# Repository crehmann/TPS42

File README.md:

# TPS42

TPS42 is a 42/36 keys ergonomic split keyboard. The outer pinky columns can be broken off. The main goal for desing it was to have a low profile split keyboard with an integrated TrackPoint module

## Features
- Integrated TrackPoint reset circuit and the option to mount a TrackPoint to the bottom of the PCB (between the two inner columns)
- I2C interface for an OLED display
- Wireless Ready (however, without TrackPoint support):
  - Battery switch / connector
  - Option to use a battery friendly Sharp memory display instead of an OLED display
- Choc-spaced
- Partially hot swap sockets supported (except for two switches around the TrackPoint module)

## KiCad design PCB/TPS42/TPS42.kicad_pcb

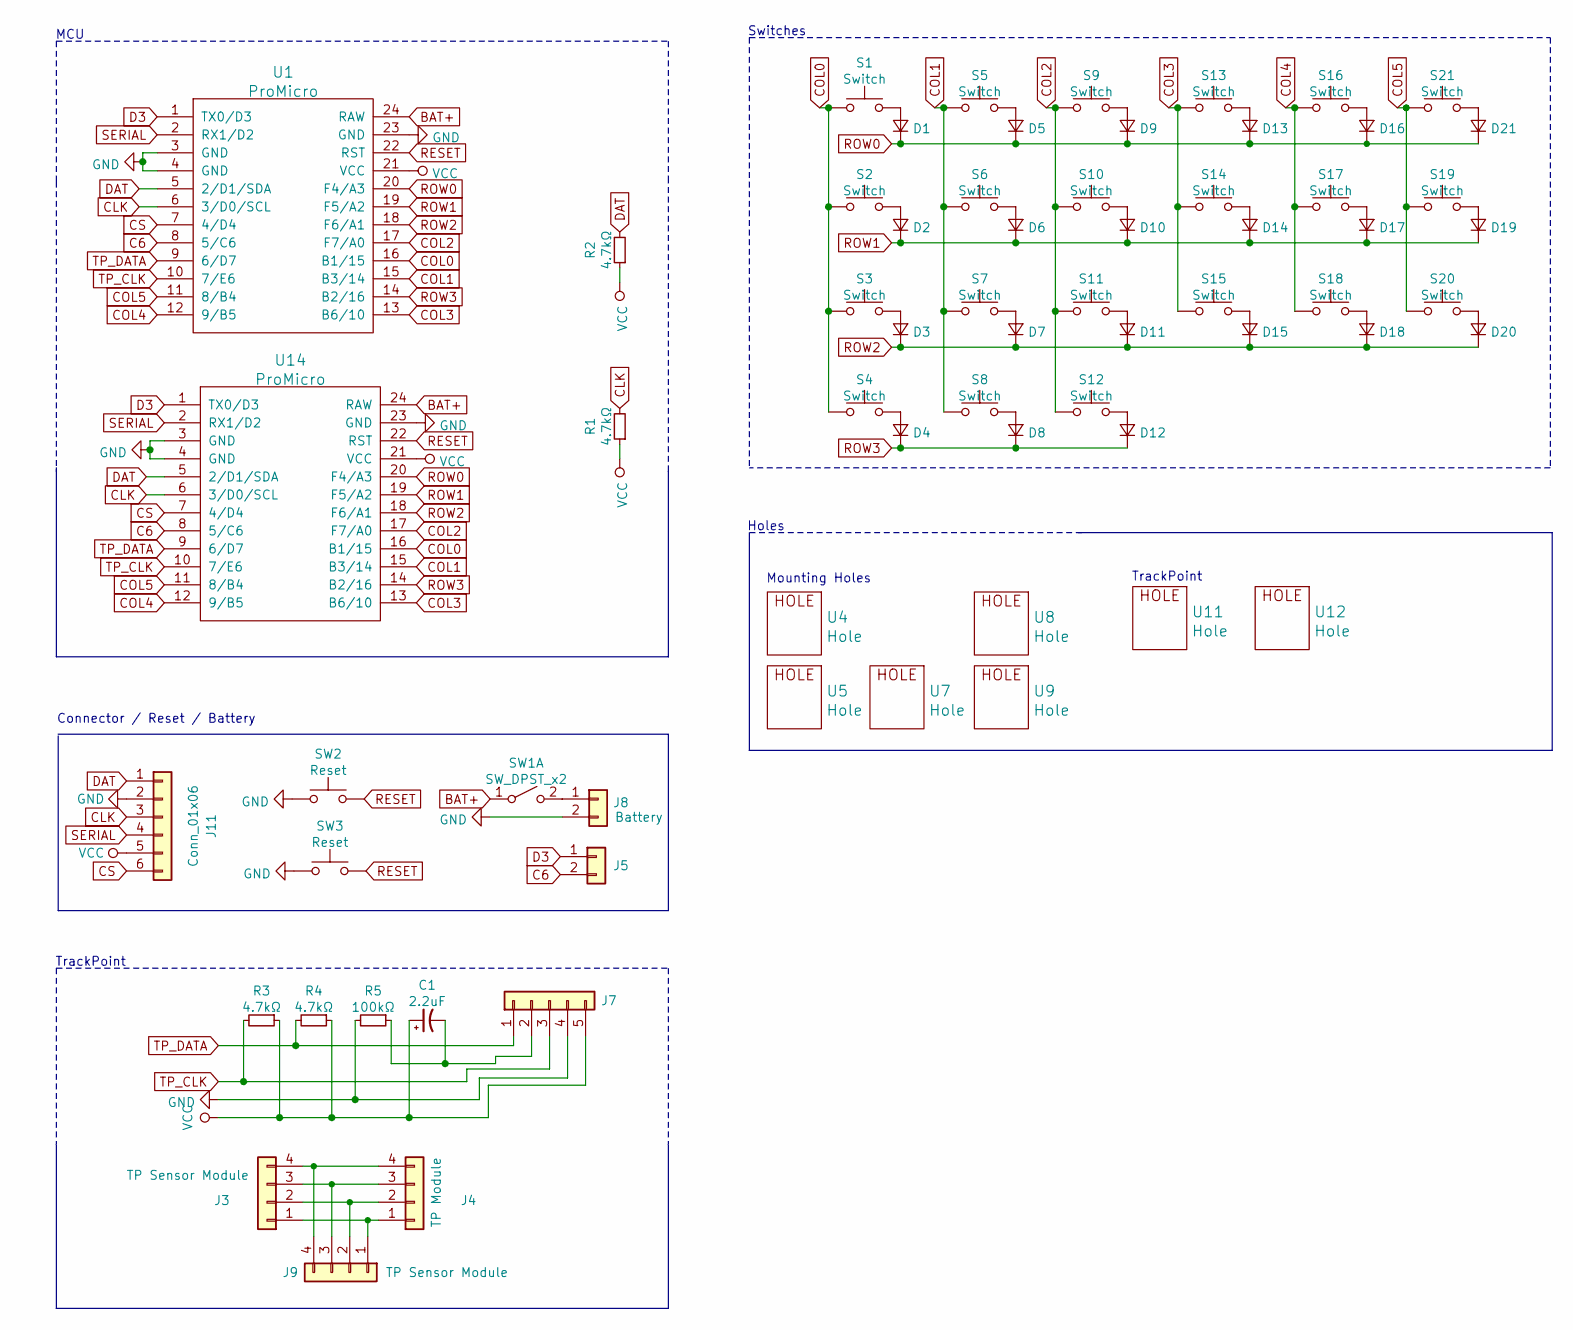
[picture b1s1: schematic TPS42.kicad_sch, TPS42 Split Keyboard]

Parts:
C1: 2.2uF; C_0603_1608Metric_Pad1.08x0.95mm_HandSolder_Reversable
D1, D2, D3, D4, D5, D6, D7, D8, D9, D10, D11, D12, D13, D14, D15, D16, D17, D18, D19, D20, D21: D_Small; D_SOD-323_HandSoldering_Reversable
J3, J9: TP Sensor Module; TPSensorModule_Connector
J4: TP Module; TPSensorModule_Connector
J5: Conn_01x02; PinHeader_1x02_P2.54mm_Vertical
J7: TrackPoint; TPModule
J8: Battery; PinHeader_1x02_P2.54mm_Vertical
J11: Conn_01x06; PinHeader_2x03_P2.54mm_Vertical
R1, R2, R3, R4: 4.7kΩ; R_0603_1608Metric_Pad0.98x0.95mm_HandSolder_Reversable
R5: 100kΩ; R_0603_1608Metric_Pad0.98x0.95mm_HandSolder_Reversable
S1, S6: Switch; SW_PG1350_reversible
S2, S3, S5, S7, S8, S9, S10, S11, S12, S13, S14, S15, S16, S17, S18, S19, S20, S21: Switch; Kailh_socket_PG1350_optional_reversible.kicad_mod
S4: Switch; Kailh_socket_PG1350_125_optional_reversible.kicad_mod
SW1: SW_DPST_x2; SW-TH_3P-L9.1-W3.5-P2.50-S3.20-A3
SW2, SW3: Reset; SMD-SW-4_5.1x5.1x2.5
U1: ProMicro; ProMicro_Flipped_v2_A
U4, U5, U7, U8, U9, U12: Hole; HOLE_M2_TH
U11: Hole; TPSensorModule
U14: ProMicro; ProMicro_Flipped_v2_B

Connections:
BAT+: SW1.1 (A), U1.24 (RAW), U14.24 (RAW)
C6: J5.2, U1.8 (5/C6), U14.8 (5/C6)
CLK: J11.3, R1.2, U1.6 (3/D0/SCL), U14.6 (3/D0/SCL)
COL0: S1.1, S2.1, S3.1, S4.1, U1.16 (B1/15), U14.16 (B1/15)
COL1: S5.1, S6.1, S7.1, S8.1, U1.15 (B3/14), U14.15 (B3/14)
COL2: S9.1, S10.1, S11.1, S12.1, U1.17 (F7/A0), U14.17 (F7/A0)
COL3: S13.1, S14.1, S15.1, U1.13 (B6/10), U14.13 (B6/10)
COL4: S16.1, S17.1, S18.1, U1.12 (9/B5), U14.12 (9/B5)
COL5: S19.1, S20.1, S21.1, U1.11 (8/B4), U14.11 (8/B4)
CS: J11.6, U1.7 (4/D4), U14.7 (4/D4)
D3: J5.1, U1.1 (TX0/D3), U14.1 (TX0/D3)
DAT: J11.1, R2.2, U1.5 (2/D1/SDA), U14.5 (2/D1/SDA)
GND: J7.4, J8.2, J11.2, R5.2, SW2.1, SW3.1, U1.3 (GND), U1.4 (GND), U1.23 (GND), U14.3 (GND), U14.4 (GND), U14.23 (GND)
unnamed: C1.2, J7.2, R5.1
unnamed: D1.2 (A), S1.2
unnamed: D2.2 (A), S2.2
unnamed: D3.2 (A), S3.2
unnamed: D4.2 (A), S4.2
unnamed: D5.2 (A), S5.2
unnamed: D6.2 (A), S6.2
unnamed: D7.2 (A), S7.2
unnamed: D8.2 (A), S8.2
unnamed: D9.2 (A), S9.2
unnamed: D10.2 (A), S10.2
unnamed: D11.2 (A), S11.2
unnamed: D12.2 (A), S12.2
unnamed: D13.2 (A), S13.2
unnamed: D14.2 (A), S14.2
unnamed: D15.2 (A), S15.2
unnamed: D16.2 (A), S16.2
unnamed: D17.2 (A), S17.2
unnamed: D18.2 (A), S18.2
unnamed: D19.2 (A), S19.2
unnamed: D20.2 (A), S20.2
unnamed: D21.2 (A), S21.2
unnamed: J3.1, J4.1, J9.1
unnamed: J3.2, J4.2, J9.2
unnamed: J3.3, J4.3, J9.3
unnamed: J3.4, J4.4, J9.4
unnamed: J8.1, SW1.2 (B)
RESET: SW2.2, SW3.2, U1.22 (RST), U14.22 (RST)
ROW0: D1.1 (K), D5.1 (K), D9.1 (K), D13.1 (K), D16.1 (K), D21.1 (K), U1.20 (F4/A3), U14.20 (F4/A3)
ROW1: D2.1 (K), D6.1 (K), D10.1 (K), D14.1 (K), D17.1 (K), D19.1 (K), U1.19 (F5/A2), U14.19 (F5/A2)
ROW2: D3.1 (K), D7.1 (K), D11.1 (K), D15.1 (K), D18.1 (K), D20.1 (K), U1.18 (F6/A1), U14.18 (F6/A1)
ROW3: D4.1 (K), D8.1 (K), D12.1 (K), U1.14 (B2/16), U14.14 (B2/16)
SERIAL: J11.4, U1.2 (RX1/D2), U14.2 (RX1/D2)
TP_CLK: J7.3, R3.2, U1.10 (7/E6), U14.10 (7/E6)
TP_DATA: J7.1, R4.2, U1.9 (6/D7), U14.9 (6/D7)
VCC: C1.1, J7.5, J11.5, R1.1, R2.1, R3.1, R4.1, U1.21 (VCC), U14.21 (VCC)

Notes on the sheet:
Holes
TrackPoint
Connector / Reset / Battery
Mounting Holes
Switches
MCU

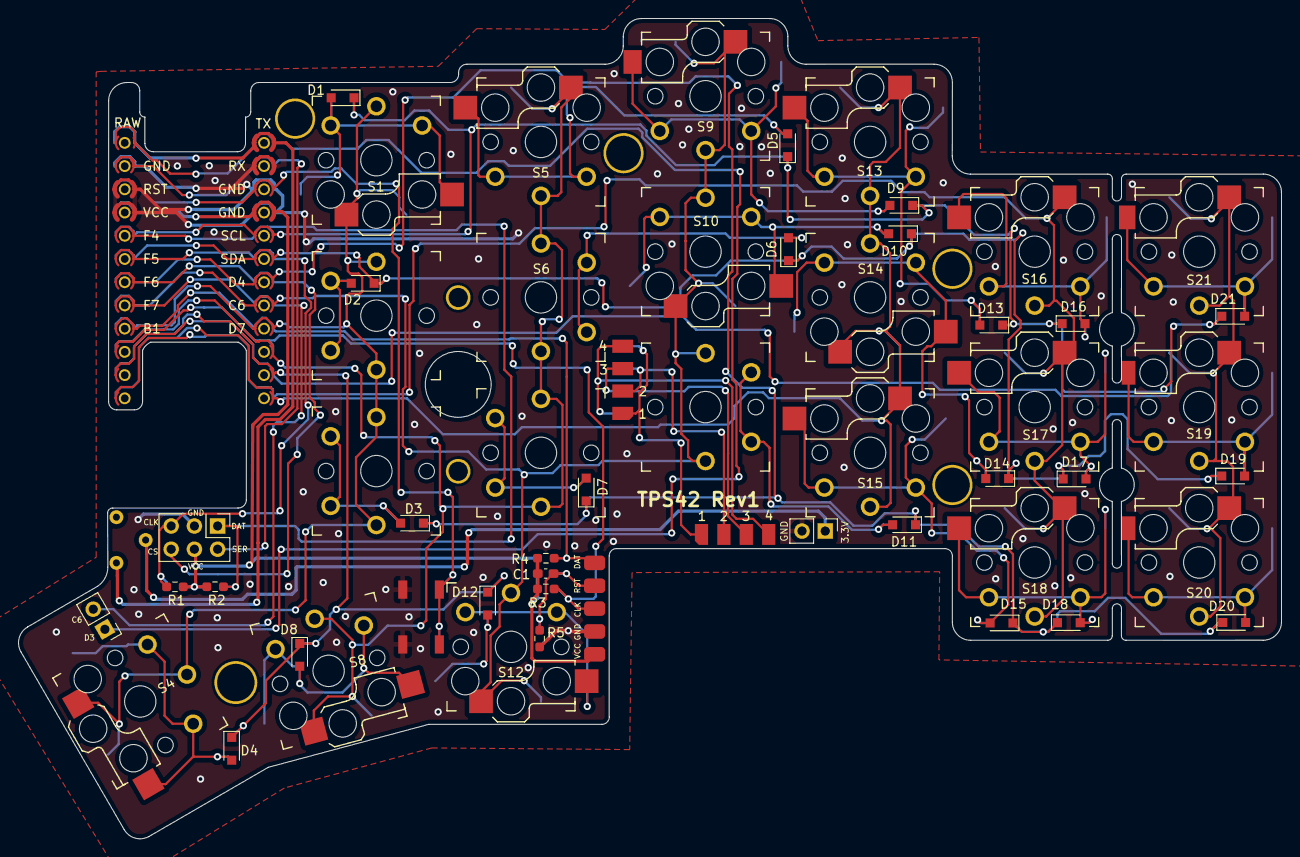
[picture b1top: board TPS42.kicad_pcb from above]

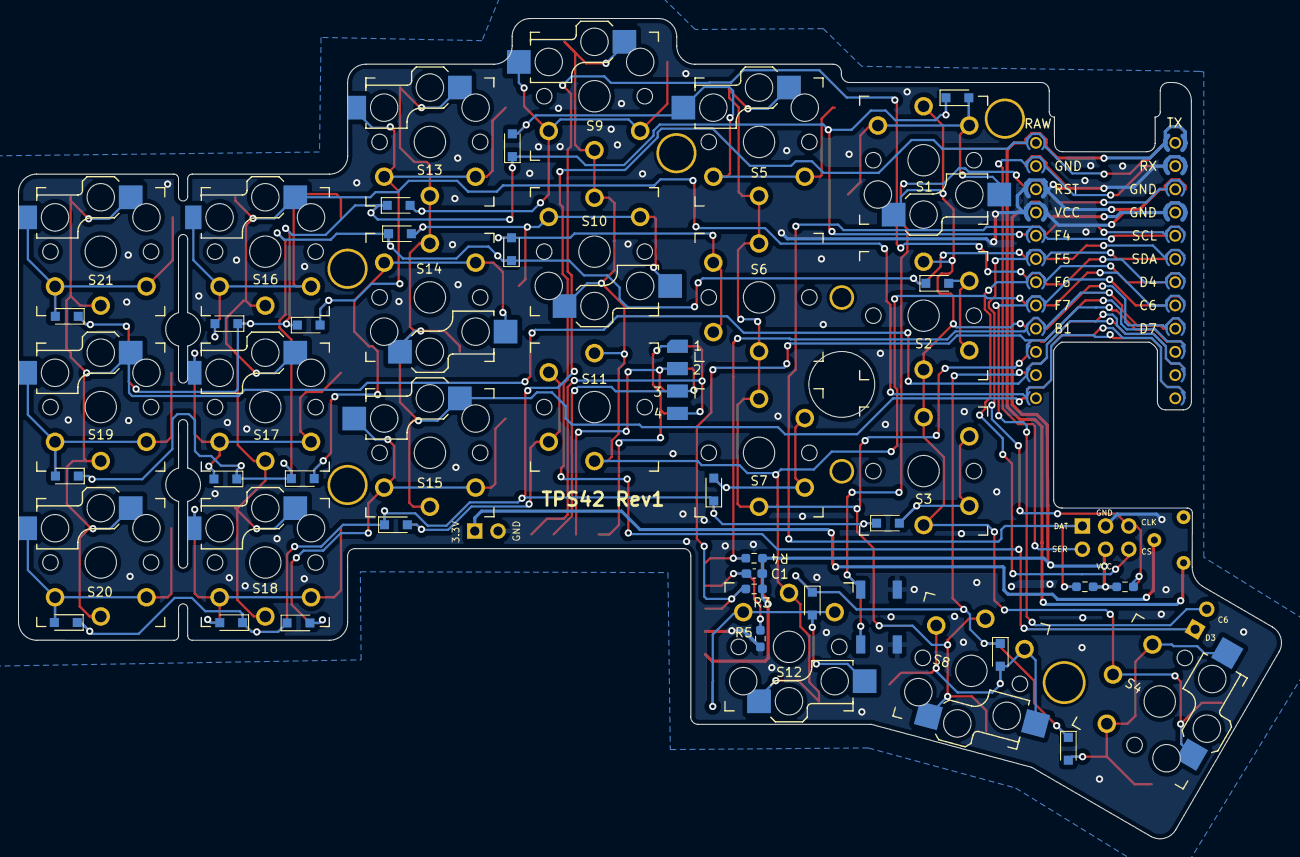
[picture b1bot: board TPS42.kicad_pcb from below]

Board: 2 copper layers, 138.1 x 89.7 mm, 66 parts (4 on the bottom side), 49 nets.

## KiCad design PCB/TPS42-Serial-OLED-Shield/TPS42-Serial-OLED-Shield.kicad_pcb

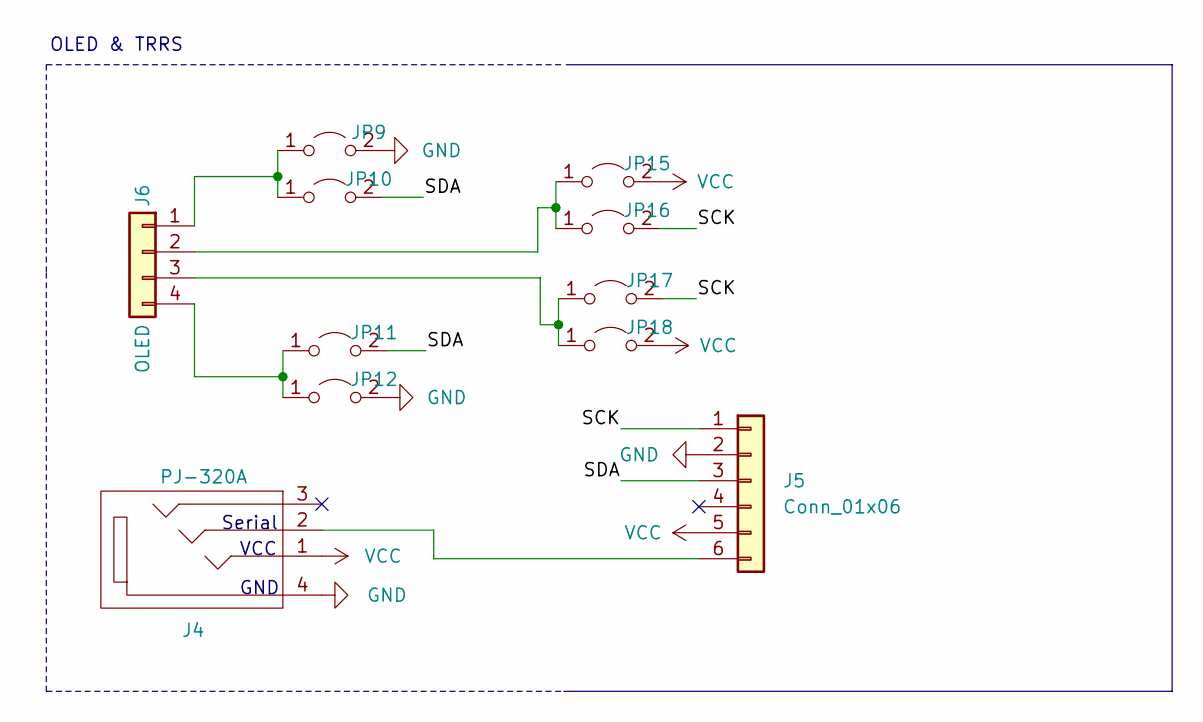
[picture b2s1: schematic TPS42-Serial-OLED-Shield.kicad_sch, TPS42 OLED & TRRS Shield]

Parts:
J4: PJ-320A; MJ-4PP-9-reversable
J5: Conn_01x06; PinHeader_2x03_P2.54mm_Vertical
J6: OLED
JP9, JP10, JP11, JP12, JP15, JP16, JP17, JP18: Jumper_2_Open; SolderJumper-2_P1.3mm_Open_TrianglePad1.0x1.5mm

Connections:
/SCK: J5.1, JP16.2 (B), JP17.2 (B)
/SDA: J5.3, JP10.2 (B), JP11.2 (B)
GND: J4.4, J5.2, JP9.2 (B), JP12.2 (B)
unnamed: J4.2, J5.6
unnamed: J6.1, JP9.1 (A), JP10.1 (A)
unnamed: J6.2, JP15.1 (A), JP16.1 (A)
unnamed: J6.3, JP17.1 (A), JP18.1 (A)
unnamed: J6.4, JP11.1 (A), JP12.1 (A)
VCC: J4.1, J5.5, JP15.2 (B), JP18.2 (B)

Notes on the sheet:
Serial
OLED & TRRS
VCC
GND

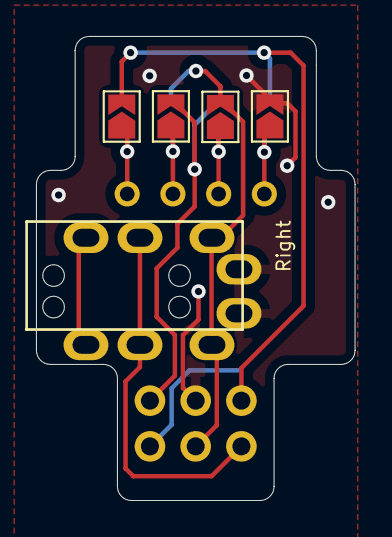
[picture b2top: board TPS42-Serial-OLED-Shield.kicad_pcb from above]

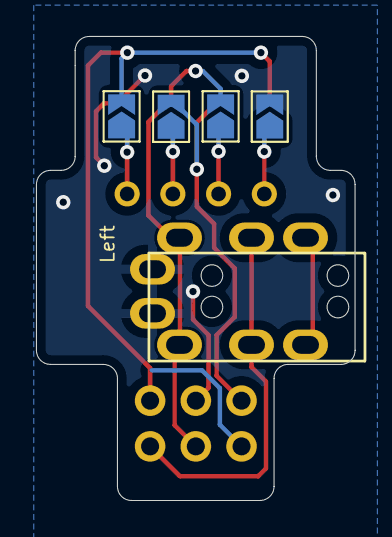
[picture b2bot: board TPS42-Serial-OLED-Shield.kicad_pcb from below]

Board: 2 copper layers, 17.7 x 25.8 mm, 11 parts (6 on the bottom side), 9 nets.

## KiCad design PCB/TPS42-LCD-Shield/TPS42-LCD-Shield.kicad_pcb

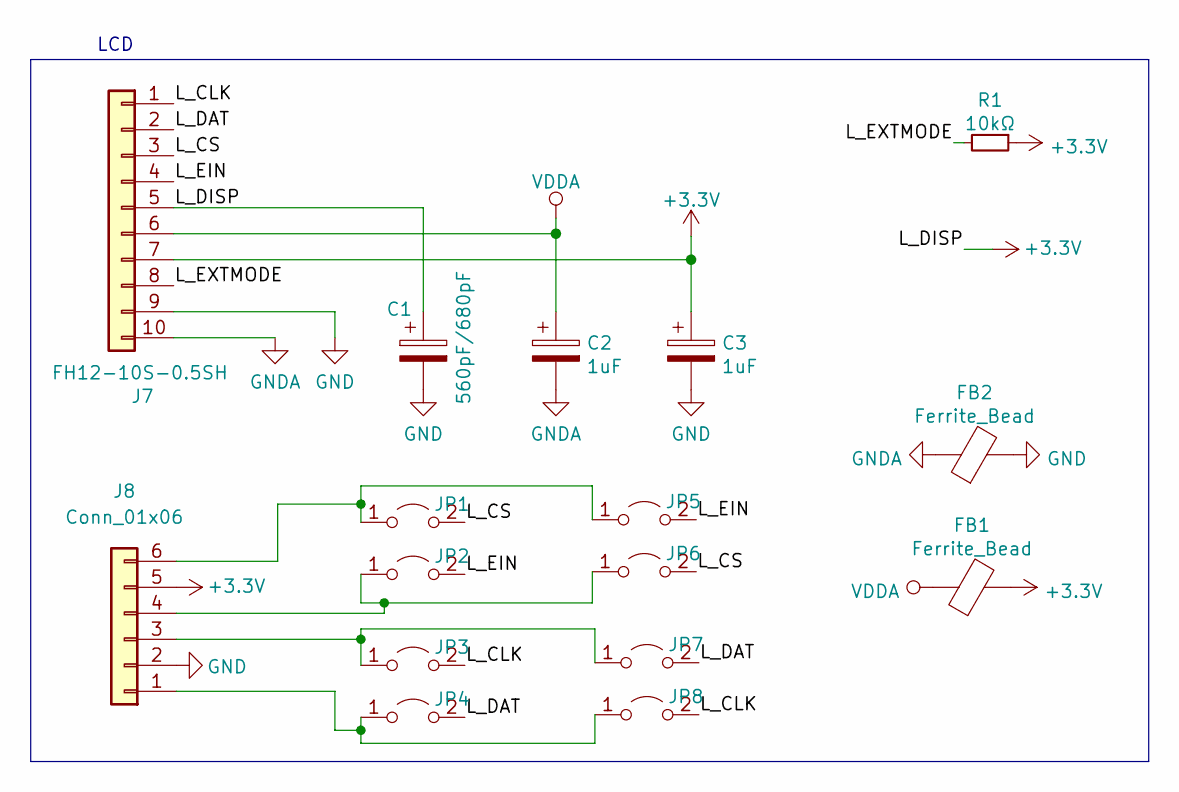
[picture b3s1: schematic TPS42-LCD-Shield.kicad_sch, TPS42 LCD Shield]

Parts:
C1: 560pF/680pF; C_0603_1608Metric_Pad1.08x0.95mm_HandSolder; LCSC C1630
C2, C3: 1uF; C_0603_1608Metric_Pad1.08x0.95mm_HandSolder; LCSC C15849
FB1, FB2: Ferrite_Bead; R_0805_2012Metric_Pad1.20x1.40mm_HandSolder; LCSC C1017
J7: FH12-10S-0.5SH; Hirose_FH12-10S-0.5SH_1x10-1MP_P0.50mm_Horizontal; LCSC C506791
J8: Conn_01x06; PinHeader_2x03_P2.54mm_Vertical
JP1, JP2, JP3, JP4, JP5, JP6, JP7, JP8: Jumper_2_Open; SolderJumper-2_P1.3mm_Open_TrianglePad1.0x1.5mm
R1: 10kΩ; R_0603_1608Metric_Pad0.98x0.95mm_HandSolder; LCSC C25804

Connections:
+3V3: C1.1, C3.1, FB1.2, J7.5, J7.7, J8.5, R1.1
/L_CLK: J7.1, JP3.2 (B), JP8.2 (B)
/L_CS: J7.3, JP1.2 (B), JP6.2 (B)
/L_DAT: J7.2, JP4.2 (B), JP7.2 (B)
/L_EIN: J7.4, JP2.2 (B), JP5.2 (B)
/L_EXTMODE: J7.8, R1.2
GND: C1.2, C3.2, FB2.2, J7.9, J8.2
GNDA: C2.2, FB2.1, J7.10
unnamed: J8.1, JP4.1 (A), JP8.1 (A)
unnamed: J8.3, JP3.1 (A), JP7.1 (A)
unnamed: J8.4, JP2.1 (A), JP6.1 (A)
unnamed: J8.6, JP1.1 (A), JP5.1 (A)
VDDA: C2.1, FB1.1, J7.6

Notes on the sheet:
LCD

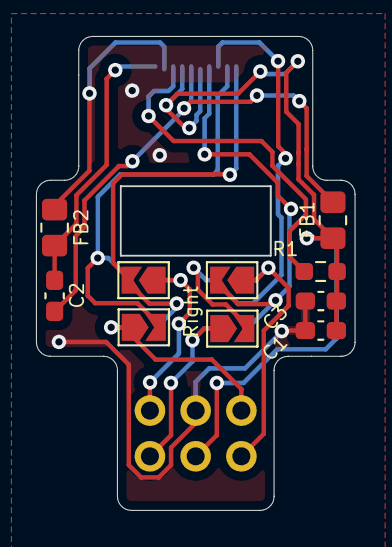
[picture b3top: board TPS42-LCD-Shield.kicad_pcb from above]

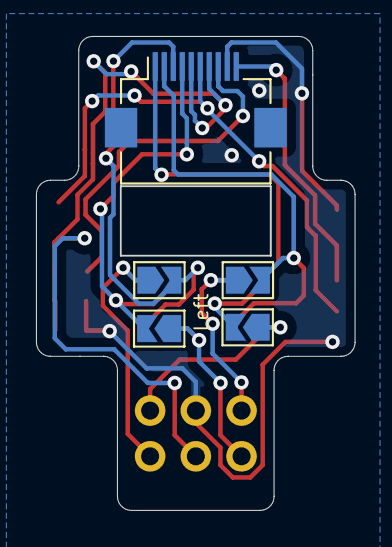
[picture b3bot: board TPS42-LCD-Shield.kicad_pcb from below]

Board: 2 copper layers, 17.7 x 26.3 mm, 16 parts (5 on the bottom side), 13 nets.

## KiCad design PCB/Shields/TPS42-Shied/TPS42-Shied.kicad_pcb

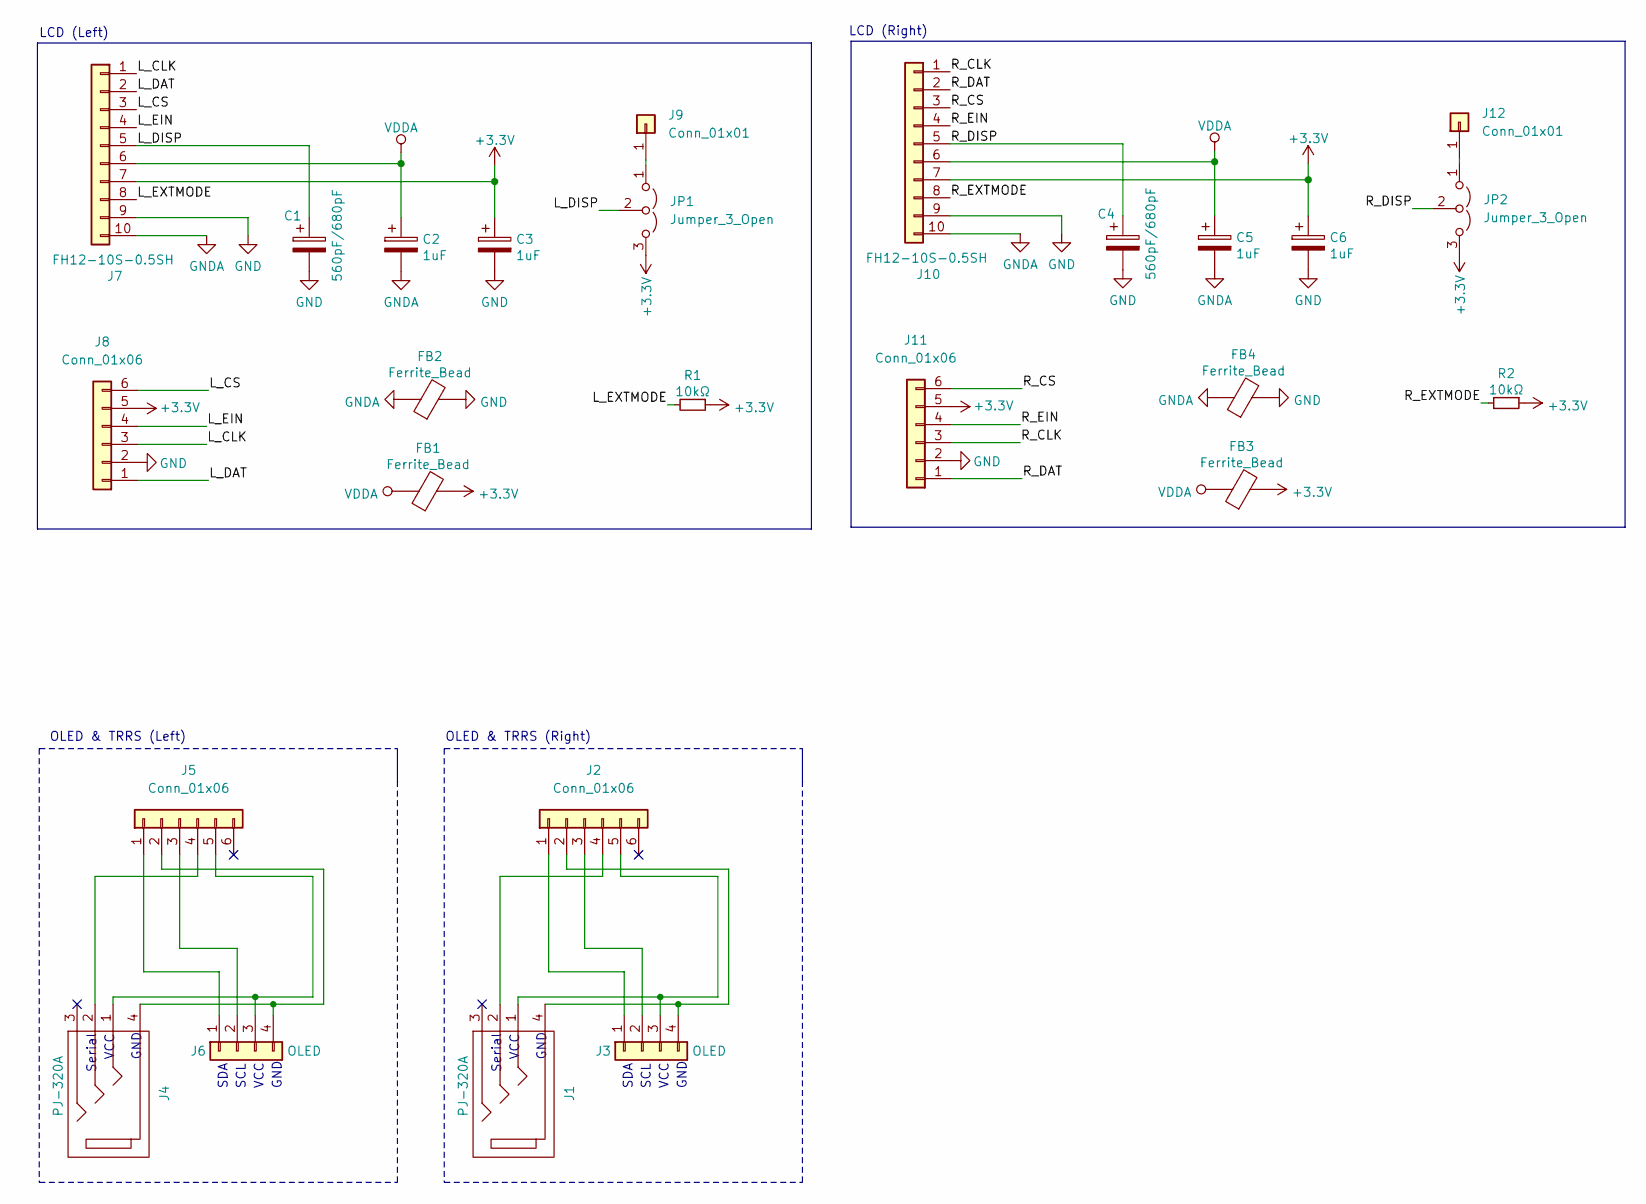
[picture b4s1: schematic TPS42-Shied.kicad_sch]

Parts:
C1, C4: 560pF/680pF; C_0603_1608Metric_Pad1.08x0.95mm_HandSolder; LCSC C1630
C2, C3, C5, C6: 1uF; C_0603_1608Metric_Pad1.08x0.95mm_HandSolder; LCSC C15849
FB1, FB2, FB3, FB4: Ferrite_Bead; R_0805_2012Metric_Pad1.20x1.40mm_HandSolder; LCSC C1017
J1, J4: PJ-320A; MJ-4PP-9
J2, J5, J8, J11: Conn_01x06; PinHeader_2x03_P2.54mm_Vertical
J3, J6: OLED
J7, J10: FH12-10S-0.5SH; Hirose_FH12-10S-0.5SH_1x10-1MP_P0.50mm_Horizontal; LCSC C506791
J9, J12: Conn_01x01; PinHeader_1x01_P2.54mm_Vertical
JP1, JP2: Jumper_3_Open; SolderJumper-3_P2.0mm_Open_TrianglePad1.0x1.5mm
R1, R2: 10kΩ; R_0603_1608Metric_Pad0.98x0.95mm_HandSolder; LCSC C25804

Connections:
+3V3: C3.1, C6.1, FB1.2, FB3.2, J7.7, J8.5, J10.7, J11.5, JP1.3 (B), JP2.3 (B), R1.1, R2.1
/L_CLK: J7.1, J8.3
/L_CS: J7.3, J8.6
/L_DAT: J7.2, J8.1
/L_DISP: C1.1, J7.5, JP1.2 (C)
/L_EIN: J7.4, J8.4
/L_EXTMODE: J7.8, R1.2
/R_CLK: J10.1, J11.3
/R_CS: J10.3, J11.6
/R_DAT: J10.2, J11.1
/R_DISP: C4.1, J10.5, JP2.2 (C)
/R_EIN: J10.4, J11.4
/R_EXTMODE: J10.8, R2.2
GND: C1.2, C3.2, C4.2, C6.2, FB2.2, FB4.2, J7.9, J8.2, J10.9, J11.2
GNDA: C2.2, C5.2, FB2.1, FB4.1, J7.10, J10.10
unnamed: J1.1, J2.5, J3.3
unnamed: J1.2, J2.4
unnamed: J1.4, J2.2, J3.4
unnamed: J2.1, J3.1
unnamed: J2.3, J3.2
unnamed: J4.1, J5.5, J6.3
unnamed: J4.2, J5.4
unnamed: J4.4, J5.2, J6.4
unnamed: J5.1, J6.1
unnamed: J5.3, J6.2
unnamed: J9.1, JP1.1 (A)
unnamed: J12.1, JP2.1 (A)
VDDA: C2.1, C5.1, FB1.1, FB3.1, J7.6, J10.6

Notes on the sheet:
VCC
Serial
GND
LCD (Right)
LCD (Left)
SDA
SCL
OLED & TRRS (Right)
OLED & TRRS (Left)

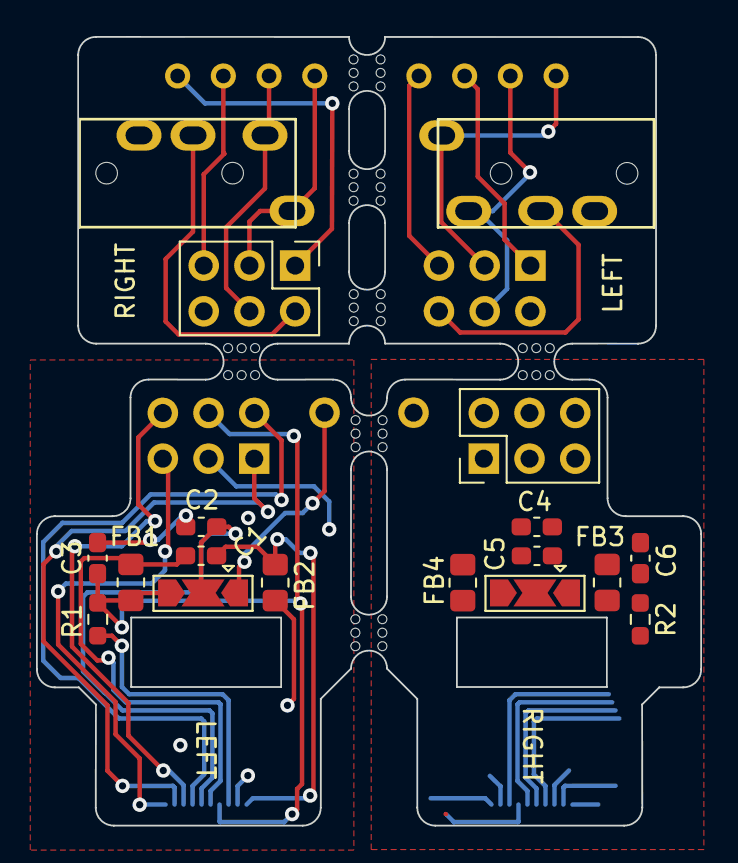
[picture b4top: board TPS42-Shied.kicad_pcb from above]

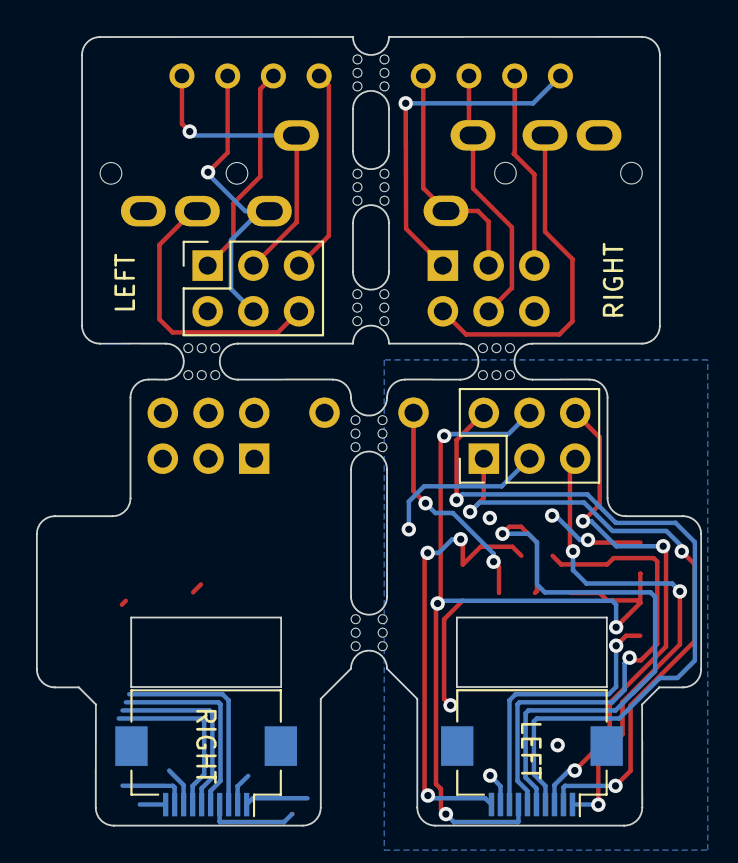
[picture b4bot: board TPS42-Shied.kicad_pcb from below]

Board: 2 copper layers, 36.9 x 43.8 mm, 33 parts (6 on the bottom side), 28 nets.

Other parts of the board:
mouse-bite-2mm-slot, mouse-bite-2mm-slot#2, mouse-bite-2mm-slot#3, mouse-bite-2mm-slot#4, mouse-bite-2mm-slot#5, mouse-bite-2mm-slot#6, mouse-bite-2mm-slot#7: VAL**; mouse-bite-2mm-slot

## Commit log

2022-05-08 Initial copy from buzzard
2022-05-08 align footprints
2022-05-08 fix switch orientation
2022-05-08 Footprint library cleanup
2022-05-08 Further footprint changes
2022-05-09 replaced diode footprint
2022-05-09 breakoff column added
2022-05-09 connected tp module
2022-05-09 place components
2022-05-09 mcu bridges
2022-05-09 Setting some labels
2022-05-10 started routing
2022-05-11 connect all mcu pins
2022-05-11 more routing
2022-05-12 and more routing
2022-05-14 and even more routing
2022-05-14 finished main pcb routing
2022-05-14 Added oled/trrs shield
2022-05-15 add left lcd shield
2022-05-15 fixed typo
2022-05-16 finish routing
2022-05-17 ignore gerber zips
2022-05-17 fix renaming
2022-05-17 center shield pins with mcu
2022-05-17 make it reversable (I)
2022-05-18 splitted shields
2022-05-18 renaming
2022-05-19 finalizing
2022-06-12 reduced with and added longer pads for fcc
2022-06-12 removed serial jumber
2022-06-15 add case outlines
2022-06-22 added outlines
2022-06-22 add labels for battery connection
2022-06-22 started with case design
2022-06-24 add cutouts for mcu and connectors
2022-06-24 prepare bottom plate
2022-06-25 add cutout for track point module and finalize bottom plate
2022-06-25 improved switch cutout
2022-06-25 added helper points
2022-06-26 reduced indentation for shield solder points
2022-07-05 fix lcd extrusion height and add additional cutouts around top plate
2022-07-07 work on wireless case
2022-07-08 fix some measurements
2022-07-10 fix usb c connector offset for wireless case and some wall thickness improvements
2022-07-24 improved wireless case power switch hole and removed display extrusion
2022-07-30 moved lcd cutout a little down and increased thumb 1.5 outline
2022-07-31 Add fr4 top plate
2022-07-31 Added FR4 Bottom Plate
2022-07-31 moved dxf files into sub directory
2022-07-31 added 3x6 option
2022-08-07 add some pictures
2022-10-25 updated images
2022-10-30 additional images
2022-11-13 moved track point a row further down
2022-11-13 modified case to match moved down TrackPoint desing
